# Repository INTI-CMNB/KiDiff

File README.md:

# KiDiff (kicad-diff)

This program generates a PDF file showing the changes between two KiCad PCB or
SCH files.

PCBs are plotted into PDF files, one for each layer. Then ImageMagick is used
to compare the layers and PNG files are generated. The PNGs are finally
assembled into one PDF file and the default PDF reader is invoked.

All the intermediate files are generated in the system temporal directory and
removed as soon as the job is finished. You can cache the layers PDFs
specifying a cache directory and keep the resulting diff images specifying an
output directory.

For SCHs the process is similar, but using KiAuto. Note that one schematic is
compared at a time. The `--all_pages` option allows comparing multiple pages.
In this case adding or removing pages is only supported when the
`rsvg-convert` tool is available. Also note that this can't be done by the git
plug-in because git extracts only the file you want to compare. Consult the
advanced use explanation.

The default resolution for the images is 150 DPI. It can be increased for
better images, at the cost of (exponentially) longer execution times. You can
provide a smaller resolution for faster processing. For high resolution you
could need to configure the ImageMagick limits. Consult the 'identify -list
resource' command.

# Installation

## Dependencies

In order to run the scripts you need:

- Python 3.5 or newer
- KiCad 5.1 or newer
- Python3 wxWidgets (i.e. python3-wxgtk4.0). This is usually installed with
  KiCad.
- ImageMagick tools (i.e. imagemagick Debian package). Used to manipulate
  images and create PDF files.
- pdftoppm tool (i.e. poppler-utils Debian package). Used to decode PDF files.
  - Alternative: Ghostscript (slower and worst results)
- rsvg-convert tool (i.e. librsvg2-bin Debian package). Needed to compare
  schematics with multiple pages. Converts SVG files to PNGs.
- xdg-open tool (i.e. xdg-utils Debian package). Used to open the PDF viewer.
- [KiAuto](https://github.com/INTI-CMNB/KiAuto/). Used to print the schematic
  in PDF format.

In a Debian/Ubuntu system you'll first need to add this
[repo](https://set-soft.github.io/debian/) and then use:

```shell
$ sudo apt-get install kidiff
```

Arch Linux can install
[kicad-pcb-diff](https://aur.archlinux.org/packages/kidiff) using the AUR
repository:

```bash
$ yay -S kidiff
```

Note: if you are using Debian, or some derived distro like Ubuntu, you can
find a Debian package in the releases section. But using the repo is simpler.

## Standalone use

1. As root run:

```shell
# make install
```

The scripts will be copied to */usr/local/bin*. If you want to install the
scripts in */usr/bin* run

```shell
# make prefix=/usr install
```

Note: if you are using Debian, or some derived distro like Ubuntu, you can
find a Debian package in the releases section.

## Docker image

You can find a docker image containing KiDiff and other KiCad tools
[here](https://github.com/INTI-CMNB/kicad_auto).

## Git plug-in

1. Install the scripts
2. To initialize a repo just run the *kicad-diff-init.py* script from the root
   of the repo.\
   This will configure the repo to read extra configuration from
   the *.gitconfig* file.\
   It will also associate the *kicad_pcb* file
   extension with the *kicad-git-diff.py* script.
3. The initialization script will create a list of layers to be excluded in
   the *.kicad-git-diff* file.\
   Review this file and adjust it to your needs.
   Lines starting with *#* will be ignored.

Once configured the tool will be used every time you do a diff using *git*.

### Temporarily disabling the git plug-in

Sometimes the graphics diff is not what you want. To disable it just invoke
`git diff` using the `--no-ext-diff` option. It will force the text mode
original diff behavior.

### Disabling the pager

Git will use a pager to allow scrolling back and forth. This could be annoying
because you must exit it, the git option `--no-pager` disables it. Example:

```shell
$ git --no-pager diff XXXXXX.kicad_pcb
```

## PDF conversion policy

On some systems (i.e. Debian) ImageMagick disables PDF manipulation in its
*policy.xml* configuration file. Comment or remove lines like this:

```
<policy domain="coder" rights="none" pattern="PDF" />
```

On Debian 11/12 this applies to the */etc/ImageMagick-6/policy.xml* and/or
*/etc/ImageMagick-7/policy.xml* file.

# Usage

The *kicad-git-diff.py* is a plug-in for *git* so you just need to configure
*git* and then it becomes transparent. If you need to create a diff between
two files outside *git* you can use the *kicad-diff.py* script.

You have to provide the name of the two PCB/SCHs to be compared. The first is
the old one, the reference, and the second is the new, the one you want to
compare. The additional command line options are:

## --help

Shows a detailed list of the available options.

## --all_pages

Compare all pages for a schematic. Note that the tool doesn't currently
support adding or removing sheets, both documents must have the same amount of
pages.

## --cache_dir

The PCB/SCH files are plotted to PDF files. One PDF file for layer. To avoid
plotting them over and over you can specify a cache directory to store the
PDFs.

## --diff_mode

Selects the mechanism used to represent the differences:

- **red_green** this is the default mode. Here we try to mimic the colored
  text mode diff tools. Things added to the *old* file are represented in
  green and things removed in red.
- **stats** in this mode all difference are represented in red. We compute the
  amount of pixels that are different, you can use this value to determine if
  the changes are significant. See the `--fuzz` and `--threshold` options.

## --exclude

Specifies the name of a file containing a list of layers to be excluded. Each
line of the file is interpreted as a layer name. An example for this file
could be:

```raw
B.Adhes
F.Adhes
Cmts.User
Eco1.User
Eco2.User
Edge.Cuts
Margin
```

You can also use the KiCad internal layer ID number. This will avoid warnings
about undefined layer names.

Note that when using the *git* plug-in the script looks for a file named
*.kicad-git-diff* at the root of the repo.

Using this you can reduce the time wasted computing diffs for empty or useless
layers.

Note that lines starting with # are skipped.

See also `--layers`

## --force_gs

KiDiff uses poppler utils if they are available. When they aren't KiDiff can
use Ghostscript. The results using poppler are better and the process is
faster, but you can choose to use Ghostscript using this option.

## --fuzz

When comparing using the *stats* mode (see `--diff_mode`) this option controls
how strict is the color comparison. The default is to tolerate 5 % of error in
the colors. Enlarge it if you want to ignore bigger differences in the colors.

## --keep_pngs

Don't remove the individual PNGs. Complements `--output_dir`. They are usually
removed as soon as we get the output PDF.

## --layers

Specifies the name of a file containing a list of layers to be included. This
option works similar to `--exclude` but we process only the layers indicated
here.

Important: when this list is only composed by layer numbers KiDiff skips any
check and uses this list of layers, even if they aren't defined in any of the
specified PCBs. Otherwise you can get warnings about names not defined.

`--layers` and `--exclude` are mutually exclusive.

## --new_file_hash

This is the equivalent of the *--old_file_hash* option used for the new
PCB/SCH file.

## --no_reader

Use it to avoid invoking the default PDF viewer. Note that you should also
provide an output directory using *--output_dir*.

The default PDF reader is invoked using *xdg-open*

## --old_file_hash

The plotted PDF files for each layer are stored in the cache directory using a
SHA1 of the PCB/SCH file as name for the directory. You can specify another
hash here to identify the old PCB/SCH file.

The *git* plug-in uses the hash provided by *git* instead of the SHA1 for the
file.

## --output_dir

Five seconds after invoking the PDF viewer the output files are removed. If
you want to keep them for later review, or five seconds isn't enough for your
system, you can specify a directory to store the generated files.

Note: individual PNGs are always removed, consult `--keep_pngs`

## --output_name

Used to complement `--output_dir`. The default name is `diff.pdf`

## --resolution

The PDF files are converted to bitmaps to be compared. The default resolution
for these bitmaps is 150 DPIs. This is a compromise between speed and
legibility. For faster compares you can use a smaller resolution. For detailed
comparison you can use a higher resolution. Be careful because the time is
increased exponentially. You can also run out of resources. In particular
ImageMagick defines some limits to the disk used for operations. These limits
can be very low for default installations. You can consult the limits using
the following command:

`identify -list resource`

Consult ImageMagick documentation in order to increase them.

## --threshold

In the *stats* mode this option can make KiDiff to return an error value if
the difference is bigger than the specified threshold. Indicating 0 means that
we don't look for errors, KiDiff always returns 0.

## -v/--verbose

Increases the level of verbosity. The default is a quite mode, specifying one
level (*-v*) you'll get information messages about what's going on. If you
increase the level to two (*-vv*) you'll get very detailed information, most
probably useful only to debug problems.

## --version

Print the script version, copyright and license.

# Advanced use

`kicad-diff.py` can be run using the `--only_cache` option. In this mode the
*new_file* argument can be the same as the *old_file* argument. This operation
is used to store the images, but skip the comparison. In order to work you
must specify a valid `cache_dir`. You should also take note of the hash used
by `kicad-diff.py`, or just provide one using the `--old_file_hash`.

You can then compare two files using the cached images, you just need to
provide the hashes you want to compare. The *old_file* and *new_file* won't be
used.

# Similar tools

## KiCad-Diff

[KiCad-Diff](https://github.com/Gasman2014/KiCad-Diff) is a diff tool for
PCBs, is more oriented to GUI use. It has support not only for `git` but also
for `fossil` and `svn`. You can navigate the diffs and get information about
added or removed items, all using a browser. And is fast (all is handled using
SVGs).

It doesn't support schematics, can't be directly used as a git plug-in
(perhaps using some wrapper), can't measure the ammout of difference and
doesn't generate a file to see the differences (only browsable).

# Credits and notes

- This script is strongly based on Jesse Vincent
  [work](https://github.com/obra/kicad-tools).
- I borrowed the command to compare two images from Brecht Machiels. In
  particular from his
  [diffpdf.sh](https://gist.github.com/brechtm/891de9f72516c1b2cbc1) tool.
- I'm not a Python programmer, stackoverflow helps me ...

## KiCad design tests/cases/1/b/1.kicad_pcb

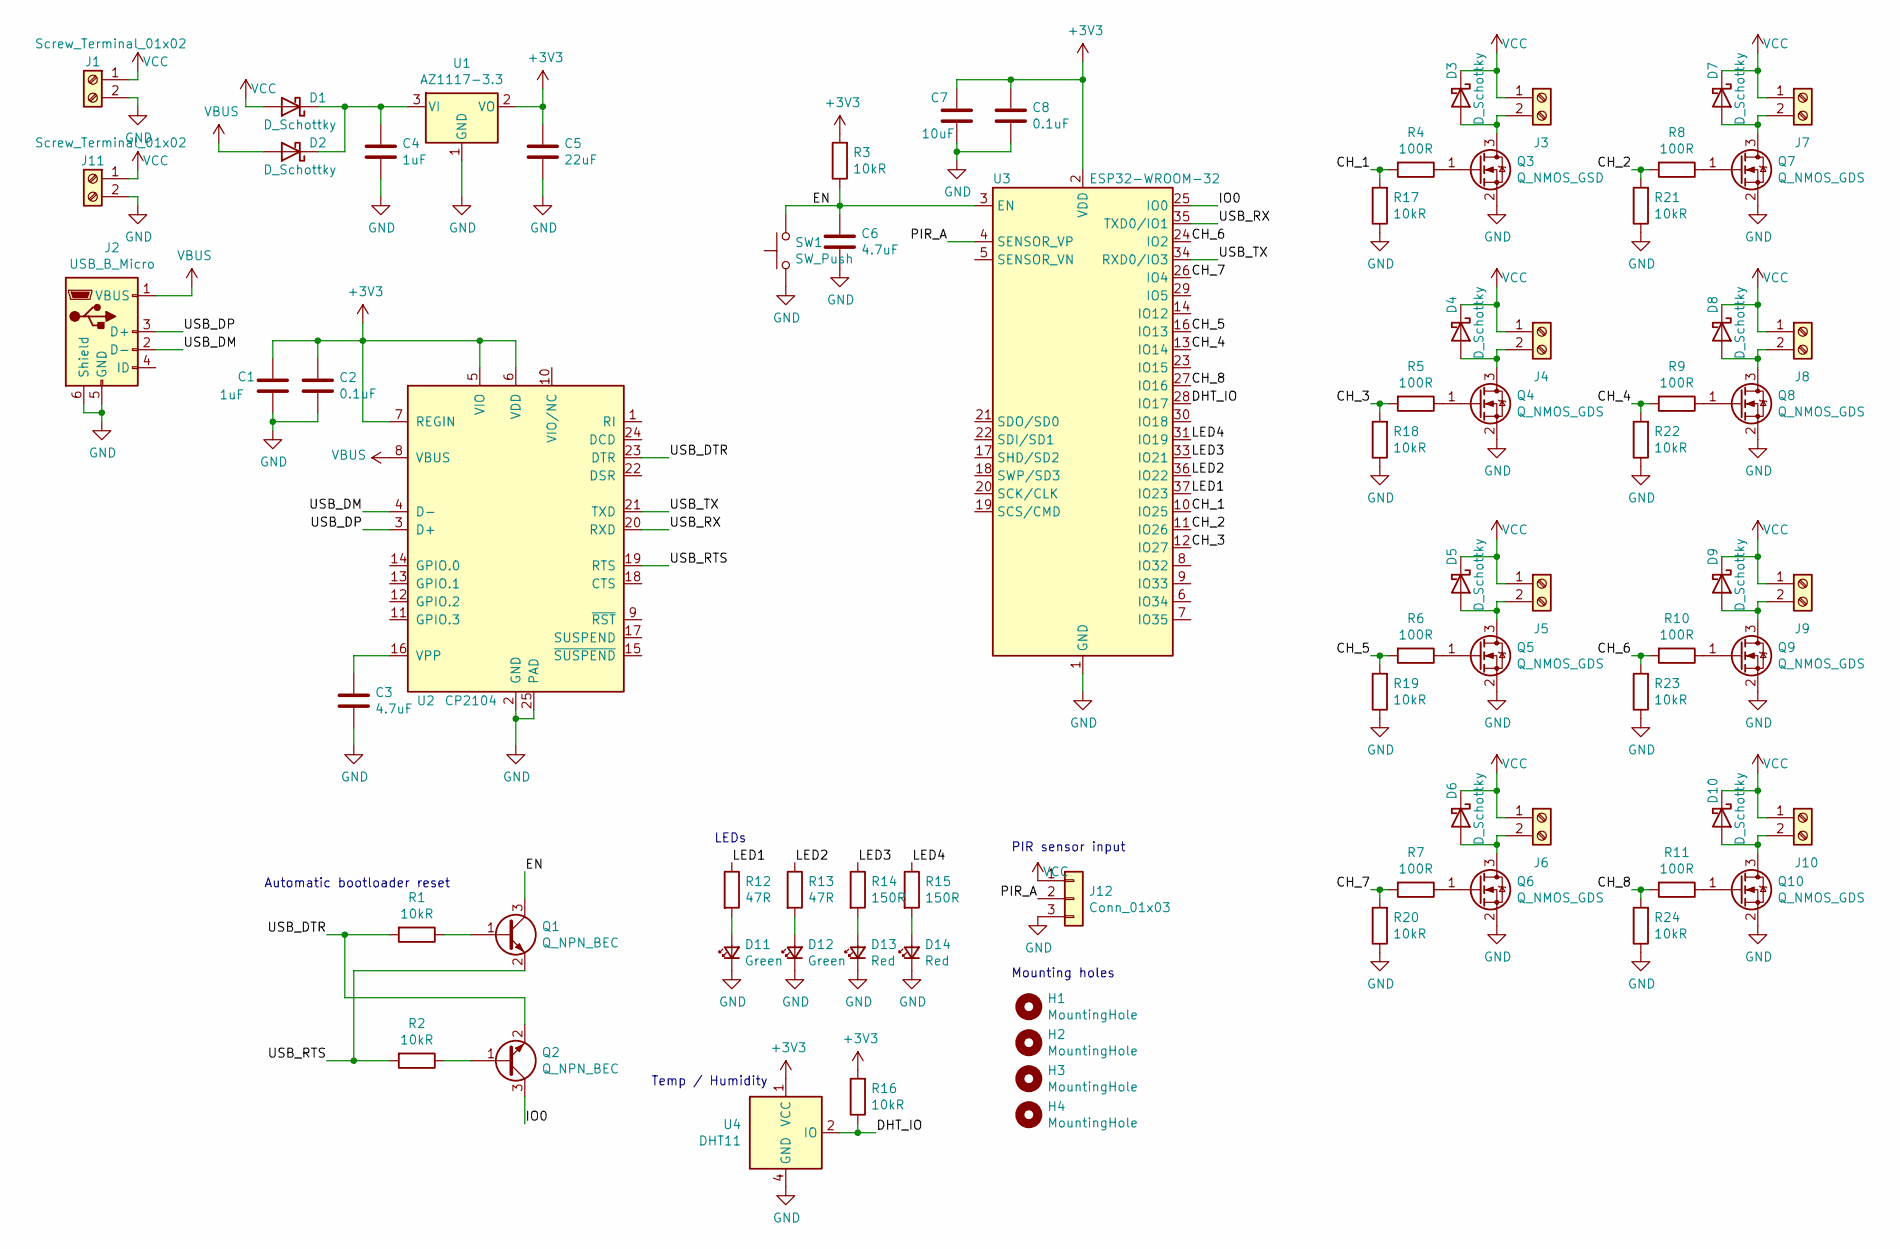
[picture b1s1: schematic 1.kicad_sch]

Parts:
C1: 1uF; R_0402_1005Metric; MPN CL05A105KA5NQNC; LCSC# C52923
C2, C8: 0.1uF; R_0402_1005Metric; MPN CL05B104KO5NNNC; LCSC# C1525
C3: 4.7uF; R_0603_1608Metric; MPN CL10A475KO8NNNC; LCSC# C19666
C4: 1uF; R_0603_1608Metric; MPN CL10A105KB8NNNC; LCSC# C15849
C5: 22uF; R_0603_1608Metric; MPN CL10A226MQ8NRNC; LCSC# C59461
C6: 4.7uF; R_0402_1005Metric; MPN CL05A475MP5NRNC; LCSC# C23733
C7: 10uF; R_0402_1005Metric; MPN CL05A106MQ5NUNC; LCSC# C15525
D1, D2, D3, D4, D5, D6, D7, D8, D9, D10: D_Schottky; D_SOD-123; MPN B5819W SL; LCSC# C8598
D11, D12: Green; LED_0603_1608Metric; MPN 19-217/GHC-YR1S2/3T; LCSC# C72043
D13, D14: Red; LED_0603_1608Metric; LCSC# C2286
H1, H2, H3, H4: MountingHole; MountingHole_3.2mm_M3
J1, J3, J4, J5, J6, J7, J8, J9, J10, J11: Screw_Terminal_01x02; TerminalBlock_Phoenix_PT-1,5-2-3.5-H_1x02_P3.50mm_Horizontal
J2: USB_B_Micro; USB_Micro-B_Molex-105017-0001
J12: Conn_01x03; JST_XH_B3B-XH-A_1x03_P2.50mm_Vertical
Q1, Q2: Q_NPN_BEC; SOT-23; MPN SS8050; LCSC# C2150
Q3: Q_NMOS_GSD; SOT-23; MPN AO3400A; LCSC# C20917
Q4, Q5, Q6, Q7, Q8, Q9, Q10: Q_NMOS_GDS; SOT-23; MPN AO3400A; LCSC# C20917
R1, R2, R3, R16, R17, R18, R19, R20, R21, R22, R23, R24: 10kR; R_0402_1005Metric; MPN 0402WGF1002TCE; LCSC# C25744
R4, R5, R6, R7, R8, R9, R10, R11: 100R; R_0402_1005Metric; MPN 0402WGF1000TCE; LCSC# C25076
R12: 47R; R_0402_1005Metric; MPN 19-217/GHC-YR1S2/3T; LCSC# C25118
R13: 47R; R_0402_1005Metric; MPN 0402WGF470JTCE; LCSC# C25118
R14, R15: 150R; R_0402_1005Metric; MPN 0402WGF1500TCE; LCSC# C25082
SW1: SW_Push; TS-1187A; MPN TS-1187A-C-D-B; LCSC# C318888
U1: AZ1117-3.3; SOT-223-3_TabPin2; MPN AZ1117CH-3.3TRG1; LCSC# C92102
U2: CP2104; QFN-24-1EP_4x4mm_P0.5mm_EP2.6x2.6mm; MPN CP2104-F03-GMR; LCSC# C47742
U3: ESP32-WROOM-32
U4: DHT11; Aosong_DHT11_5.5x12.0_P2.54mm

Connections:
+3V3: C1.1, C2.1, C5.1, C7.1, C8.1, R3.2, R16.2, U1.2 (VO), U2.5 (VIO), U2.6 (VDD), U2.7 (REGIN), U3.2 (VDD), U4.1 (VCC)
/CH_1: R4.2, R17.2, U3.10 (IO25)
/CH_2: R8.2, R21.2, U3.11 (IO26)
/CH_3: R5.2, R18.2, U3.12 (IO27)
/CH_4: R9.2, R22.2, U3.13 (IO14)
/CH_5: R6.2, R19.2, U3.16 (IO13)
/CH_6: R10.2, R23.2, U3.24 (IO2)
/CH_7: R7.2, R20.2, U3.26 (IO4)
/CH_8: R11.2, R24.2, U3.27 (IO16)
/DHT_IO: R16.1, U3.28 (IO17), U4.2 (IO)
/EN: C6.1, Q1.3 (C), R3.1, SW1.2, U3.3 (EN)
/IO0: Q2.3 (C), U3.25 (IO0)
/LED1: R12.1, U3.37 (IO23)
/LED2: R13.1, U3.36 (IO22)
/LED3: R14.1, U3.33 (IO21)
/LED4: R15.1, U3.31 (IO19)
/PIR_A: J12.2, U3.4 (SENSOR_VP)
/USB_DM: J2.2 (D-), U2.4 (D-)
/USB_DP: J2.3 (D+), U2.3 (D+)
/USB_DTR: Q2.2 (E), R1.2, U2.23 (DTR)
/USB_RTS: Q1.2 (E), R2.2, U2.19 (RTS)
/USB_RX: U2.20 (RXD), U3.35 (TXD0/IO1)
/USB_TX: U2.21 (TXD), U3.34 (RXD0/IO3)
GND: C1.2, C2.2, C3.2, C4.2, C5.2, C6.2, C7.2, C8.2, D11.1 (K), D12.1 (K), D13.1 (K), D14.1 (K), J1.2, J2.5 (GND), J2.6 (Shield), J11.2, J12.3, Q3.2 (S), Q4.2 (S), Q5.2 (S), Q6.2 (S), Q7.2 (S), Q8.2 (S), Q9.2 (S), Q10.2 (S), R17.1, R18.1, R19.1, R20.1, R21.1, R22.1, R23.1, R24.1, SW1.1, U1.1 (GND), U2.2 (GND), U2.25 (PAD), U3.1 (GND), U3.15 (GND), U3.38 (GND), U3.39 (GND), U4.4 (GND)
unnamed: C3.1, U2.16 (VPP)
unnamed: C4.1, D1.1 (K), D2.1 (K), U1.3 (VI)
unnamed: D3.2 (A), J3.2, Q3.3 (D)
unnamed: D4.2 (A), J4.2, Q4.3 (D)
unnamed: D5.2 (A), J5.2, Q5.3 (D)
unnamed: D6.2 (A), J6.2, Q6.3 (D)
unnamed: D7.2 (A), J7.2, Q7.3 (D)
unnamed: D8.2 (A), J8.2, Q8.3 (D)
unnamed: D9.2 (A), J9.2, Q9.3 (D)
unnamed: D10.2 (A), J10.2, Q10.3 (D)
unnamed: D11.2 (A), R12.2
unnamed: D12.2 (A), R13.2
unnamed: D13.2 (A), R14.2
unnamed: D14.2 (A), R15.2
unnamed: Q1.1 (B), R1.1
unnamed: Q2.1 (B), R2.1
unnamed: Q3.1 (G), R4.1
unnamed: Q4.1 (G), R5.1
unnamed: Q5.1 (G), R6.1
unnamed: Q6.1 (G), R7.1
unnamed: Q7.1 (G), R8.1
unnamed: Q8.1 (G), R9.1
unnamed: Q9.1 (G), R10.1
unnamed: Q10.1 (G), R11.1
VBUS: D2.2 (A), J2.1 (VBUS), U2.8 (VBUS)
VCC: D1.2 (A), D3.1 (K), D4.1 (K), D5.1 (K), D6.1 (K), D7.1 (K), D8.1 (K), D9.1 (K), D10.1 (K), J1.1, J3.1, J4.1, J5.1, J6.1, J7.1, J8.1, J9.1, J10.1, J11.1, J12.1

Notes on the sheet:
PIR sensor input
Automatic bootloader reset
Mounting holes
Temp / Humidity
LEDs

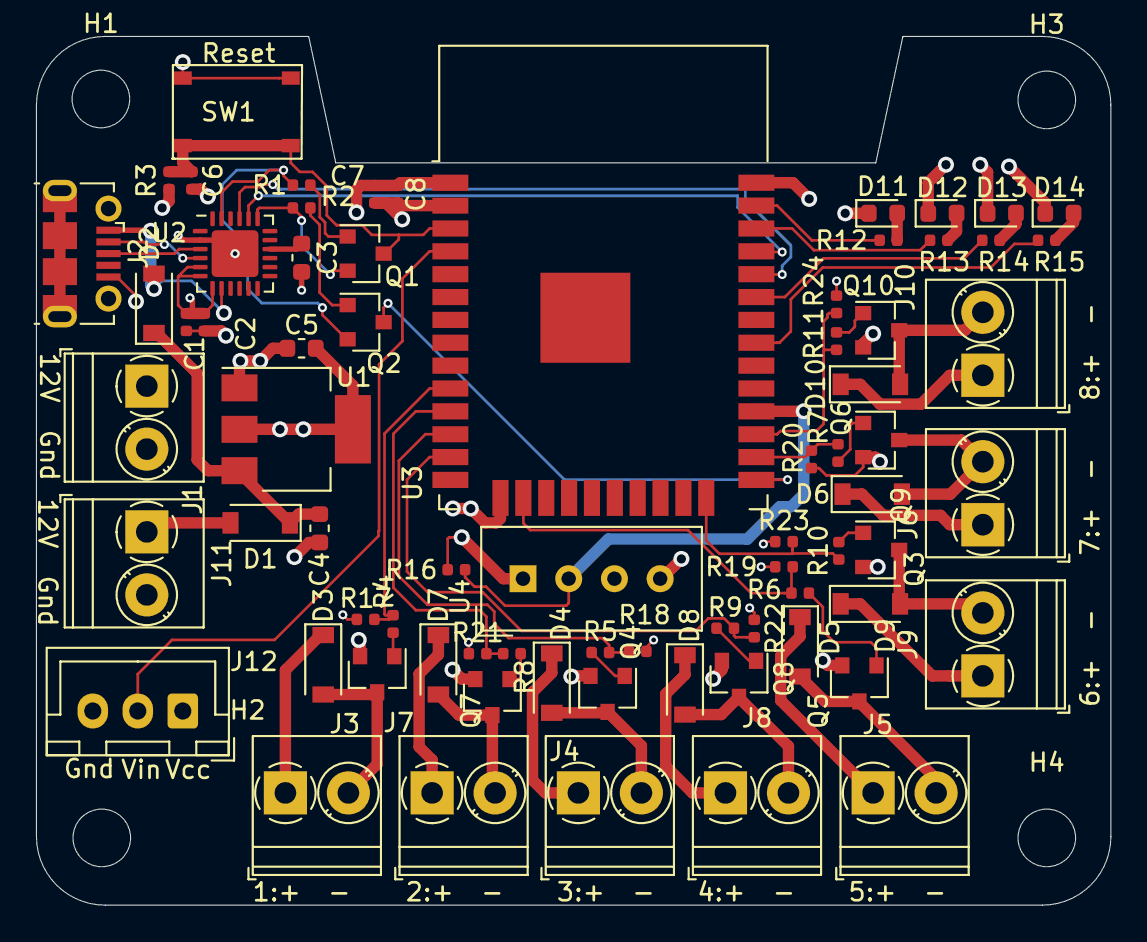
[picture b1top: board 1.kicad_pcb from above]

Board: 4 copper layers, 59.7 x 48.3 mm, 77 parts (0 on the bottom side), 50 nets.

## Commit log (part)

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2020-03-02 Added first working version of the scripts and some documentation.
2020-03-03 Added a simple makefile for installation
2020-03-03 Added Debian package files
2020-03-03 Fixed the $ sign in the README.md
2020-03-03 Added script to init the repo. Changed version to 1.1.0.
2020-03-03 Added a note about the availability of .deb packages.
2022-08-13 Added KiCad 6 support
2022-08-13 Adapted to pass flake8
2022-08-13 Bumped version to 1.2.0
2022-08-13 Removed python3-wxgtk4.0 as dependency, this is KiCad's dep
2022-08-13 Added Makefile targets to create the Debian package
2022-08-14 Added SCH support
    - Bumped version to 2.0.0
    - Removed PCB from the name
2022-08-14 Adapted the README.md
2022-08-14 Add pre-commit, fix 'ploting' typo
2022-08-15 Added "stats" mode
    - Compares using AE mode
    - Also added support for GS as alternative to Poppler
    - Bumped version to 2.1.0
2022-08-15 Fixed typos
2022-08-15 Converted old string formatting (%) to the new .format
2022-08-15 Disabled mypy
2022-08-15 Reformated the README.md
2022-08-15 Disabled black and pylint
    - Too intrusive
2022-08-22 Added support for multiple schematic pages.
2022-08-22 Removed individual PNGs for the output diff
2022-08-22 Added option to select the output file name
2022-08-22 [DOCs] Documented the --output_name option
2022-08-22 Added option to keep the individual PNGs.
2022-08-22 Changed nargs=1 by type=str, simpler
2022-08-23 Changed name to KiDiff (shorter and more clear)
2022-08-23 Changed the error codes for old/new file invalid.
    - The old ones are the reserved by Python.
2022-08-23 Added option to just populate the cache
2022-08-23 Ignore the Python cache
2022-08-23 Added Python installation script
2022-08-23 Added CHANGELOG.md
2022-08-23 Added release and PyPi GitHub workflows
2022-08-23 Bumped version to 2.2.0
2022-08-23 Changed the Debian package name to kidiff
2022-08-23 Added the old name of the Debian package as conflict
2022-08-23 Enlarged the remove delay to 5 seconds
    - Also fixed flake8 details
2022-08-24 Added support for layer numbers in the exclude file.
2022-08-24 Adjusted release date
2022-08-25 [DOCs] Documented all options
2022-08-25 Changed the red/green colors to match text mode diff tools
2022-08-25 Added support for adding/removing PCB layers
2022-08-25 Bumped version to 2.3.0
2022-08-25 Added option to specify the layers to use, instead of excluded
2022-08-25 Updated the CHANGELOG for a release
2022-08-25 Fixed KiCad 5 problems with inner layers (undefined names)
2022-08-25 Bumped version to 2.3.1
2022-08-26 Added support for multisheet files with added/removed pages.
    - Only works if rsvg-convert is installed.
    - Not for the git plug-in
2022-08-26 Added rsvg-convert as dependency
2022-08-26 Bumped version to 2.4.0
2022-08-27 Add AUR link
2022-08-29 [DOCs] Updated Debian instructions
    - The package is in the repo now
2022-08-30 [Fixed] The 'only in XXX' message
    - Worked only the first time, after caching the files it wasn't
    informed anymore.
2022-08-30 Now PCB layers are cached by layer ID, not name.
    - So changes in the names doesn't affect the process
2022-08-30 Added support for user defined layer names.
2022-08-30 Now lines in ex/include lists that begin with # are just ignored.
    - Before we let them fail to match because the names weren't valid.
    - This avoids confusing warnings.
2022-08-30 Documented how to get the text diff
2022-08-30 [Tests] First try to add some automatic tests
2022-08-30 [Tests] Removed KiCad 5 tests, we are only testing KiCad 6
2022-08-31 [Debian] Don't run tests before creating the .deb
    - They run separately
2022-08-31 [Flake8] Fixed small details
2022-08-31 Fixed problems when using the cache and the PCBs didn't have the same layers
2022-08-31 [DOCs] Updated CHANGELOG for release
2022-08-31 Bumped version to 2.4.2 (to differentiate)
2022-08-31 [Fixed] Problems when using the plug-in and comparing uncommited stuff
    - Git uses 0 as hash and hence all uncommitted stuff looks the same
2022-08-31 [DOCs] Explained how to disable git pager
2022-08-31 [DOCs] Adde mention to KiCad-Diff project
2022-10-05 Added option to skip pages without differences
2022-10-05 Updated changelog
2022-10-05 Updated Debian version
2022-10-05 [CI/CD] No need to trigger KiBot until images are updated
2022-10-05 Bumped version to 2.4.3 to differentiate
2022-10-14 Added option to skip the test for input files.
    - Useful to compare from cache.
2022-10-14 Allow to compare two multi-page schematics with different name
    - When comparing multiple sheets using the SVG mode the displayed name
    of the sheet is like the sheet path displayed by KiCad
2022-10-14 Adapted Debian time stamp
2023-02-13 [Added] KiCad v7 support
2023-02-13 Allow to use with kicad-nightly
2023-03-07 When the bounding box of the PCB changes we make the diff using a 1:1 plot
    - Not using autoscale
    - This produces something easier to understand
    Closes #4
2023-03-07 [Tests] Fixed KiCad version detection
2023-03-07 Fixed name clarification
    - Added twice because of un/scaled generation
2023-03-29 Better behavior when using different page sizes
    - Specially in the red_green mode, it failed.
    - Now we inform it.
2023-03-29 Changed status to "production"
2023-03-29 Bumped version to 2.4.6
2023-03-29 Fixed the message about different page size
2023-03-29 Bumped version to 2.4.7
2023-05-13 [Fixed] Do not linger unused pngs in the output dir
    When using `--only_different`, some page PNGs are generated and only then
    decided to be skipped. To not include them in the resulting PDF, these
    are not included in the `files` array, but this also means they are
    never deleted (regardless of whether `--keep_pngs` is passed).
    This commit removes these pngs again immediately so they not linger
    around. This also means that they are not kept with `--keep_pngs`, but
2023-10-30 [DOCs][Added] Note about ImageMagick policy issues
    Closes #7
2023-11-30 KiRi SVGs generation
    - Experimental
    - Bumped version to 2.5.0
2023-11-30 [Tests] Switching to KiCad 7 images
2023-11-30 [Tests] Relaxed pixel differences
    - Getting smaller font render errors
2023-11-30 [Tests] Reverted the tolerance
2023-11-30 [Tests] Updated references to Debian 12 tools
2023-11-30 [Tests][CI/CD] Moved to checkout@v3 GitHub Action
2023-11-30 [Makefile] Allow prefix and PYTEST override
2023-12-11 [KiRi Mode] Keep the names of the sheets as generated by KiCad
2023-12-18 [Fixed] PNGs not removed
    - For pages/layers without difference and using --only_different
    Fixes #9
2023-12-22 [Added] Option to un/fill zones
    Closes #8
2023-12-22 Bumped version to 2.5.1
2024-01-03 Updated to 2.5.1 release
2024-01-04 Bumped version to 2.5.2
2024-01-04 Smarter cache
    Changing KiCad or --zones option invalidates the cache
2024-01-07 Add pre-commit workflow + update hooks
2024-01-08 [Fixed] Typos
    - Also a few style details
2024-01-08 [Pre Commit] Adjusts
    - Removed: PyUpgrade, might reduce backwards compatibility
    - Excluded: CHANGELOG.md might interfere with parser
2024-01-09 [KiRi Mode][Fixed][KiCad 5] We can't plot the worksheet
    Bug in Python API
2024-01-09 [DOCs] Updated the changelogs for release
2024-01-10 [Added] New 2color mode
    - Needed for people that have problems to distinguish between red/green/black
    - Bumped version to 2.5.3
2024-03-04 [DOCs] Added reference to kicad_auto
    See #12
2024-03-04 [DOCs] Reformated the README
2024-05-02 Fixed flake8 issues
2024-05-02 Changed setup.py to avoid importing the source
    Broke pip on Debian 12
2024-05-03 [KiCad 8][Added] Workaround for 8.0.2 hidden text
    If the user asked to see it in the GUI the Plot controller will
    compute it as visible, even when it won't be printed at all
    because it belongs to other layer
2024-05-03 [Tests][References][KiCad 7.0.11] Updated
2024-09-04 Updated upload/download-artifact version
2024-09-12 [Added] Better drill marks handling
    KiCad 8.0.4 now makes them very visible on technical layers
2024-09-12 Bumped version to 2.5.5
2024-11-26 [DOCs][Fixed] Stray backquote
    Fixes #15
2025-01-08 Experimental KiCad 9 support, bump version to 2.5.6
2025-01-08 [CI/CD] Adapted release to the new GitHub syntax
2025-02-11 Fixes for KiCad 9 support, bump version to 2.5.7
2025-03-20 [README][Fixed] References to kicad_pcb*
    No longer exists
2025-03-20 [Plug-in][Changed] compare all the schematic pages
    Helps to workaround bugs in KiCad 9 and IMHO is better.
    See #16
2025-03-20 Bumped version to 2.5.8
2025-03-21 When debugging, print also debug output from eescheme_do
2025-03-22 Add pass of multiple -vvvv, fix missing logger
2025-03-22 Add verbosity shift for ext tools
2025-03-25 [Added][CHANGELOG] Entry for #17
2025-04-03 [Added] Workaround for SetPlotOnAllLayersSelection change
    KiCad 9.0.1 is full of API changes
2025-07-11 Add Imagemagick 7 compatibility
2025-07-11 Add check for font availability
2025-07-14 [Added] Better message when PNG conversion fails
2025-07-14 [Tests] Migrated to KiCad 9
2025-07-14 [Test] Adjust 1 (fonts)
2025-07-14 [Tests] Adjust 2 (font)
2025-07-14 [ImageMagick][Changed] Font detection
    - 7: try using `NimbusSans-Regular`, which provides Helvetica on Debian 12
    - 6: Also detect the font, but using `convert` command
    - Added debug log of command and font
2026-04-17 [Fixed] Removed log error message
2026-04-17 Bumped version to 2.5.9
2026-04-23 [Changelog] Updated
2026-04-23 [CI/CD] Updated and fixed details in tests
    - Using GitHub container
    - Fixed name of artifact 6 -> 9
    - Updated GitHub action versions
2026-04-23 [Tests] Now using KiCad 9 names
    First font adjust
2026-04-23 [flake8] Fixed issues
2026-04-23 [Makefile][Added] Lint target
2026-04-23 [Tests][References] Updated
2026-04-23 [CI/CD] Updated GitHub actions verisions
2026-04-23 [Changelog] Updated release date
2026-05-19 PDF Viewer will stay open after python script is finished
2026-05-19 Bumped version to 2.5.10
    - Fixed flake8 issues
    - Updated CHANGELOG.md
2026-05-29 [Added][KiCad 10] Support for native variants
2026-05-29 Bumped version to 2.6.0
2026-06-01 Updated version info for release
2026-06-01 [CI/CD][Release][Fixed] Package path
